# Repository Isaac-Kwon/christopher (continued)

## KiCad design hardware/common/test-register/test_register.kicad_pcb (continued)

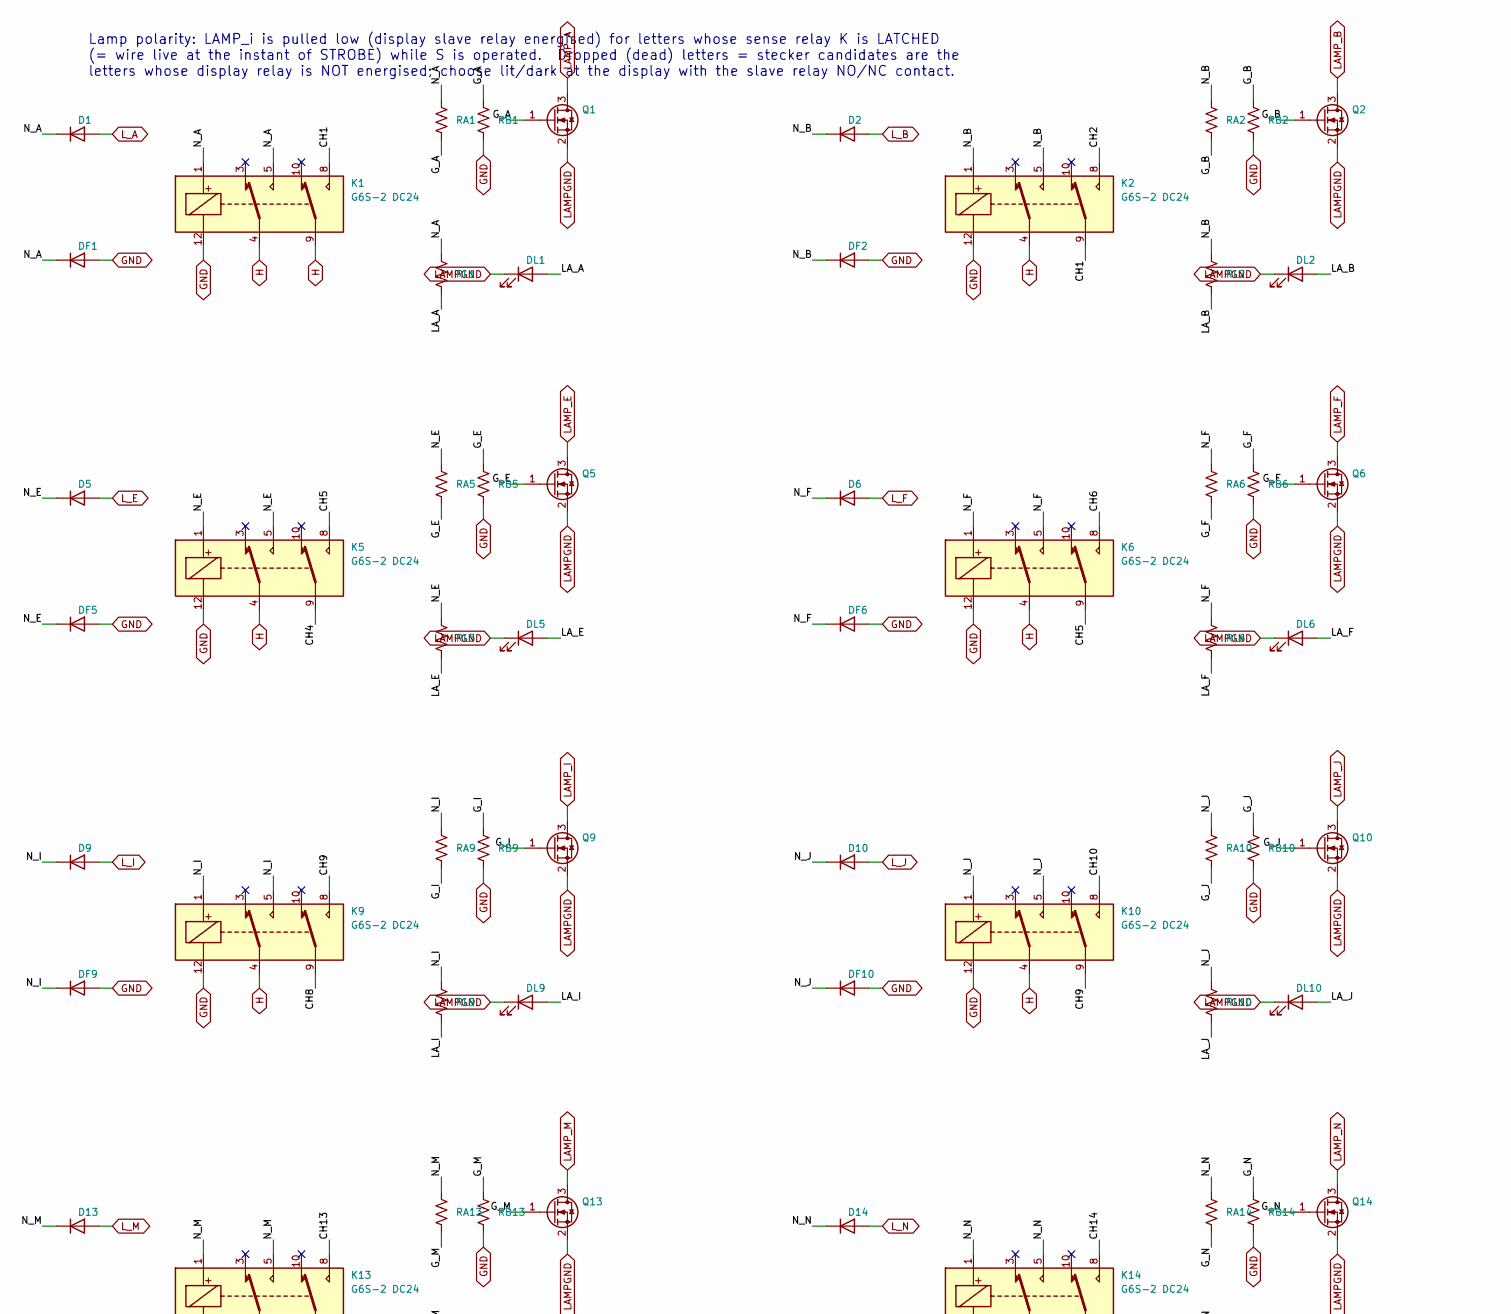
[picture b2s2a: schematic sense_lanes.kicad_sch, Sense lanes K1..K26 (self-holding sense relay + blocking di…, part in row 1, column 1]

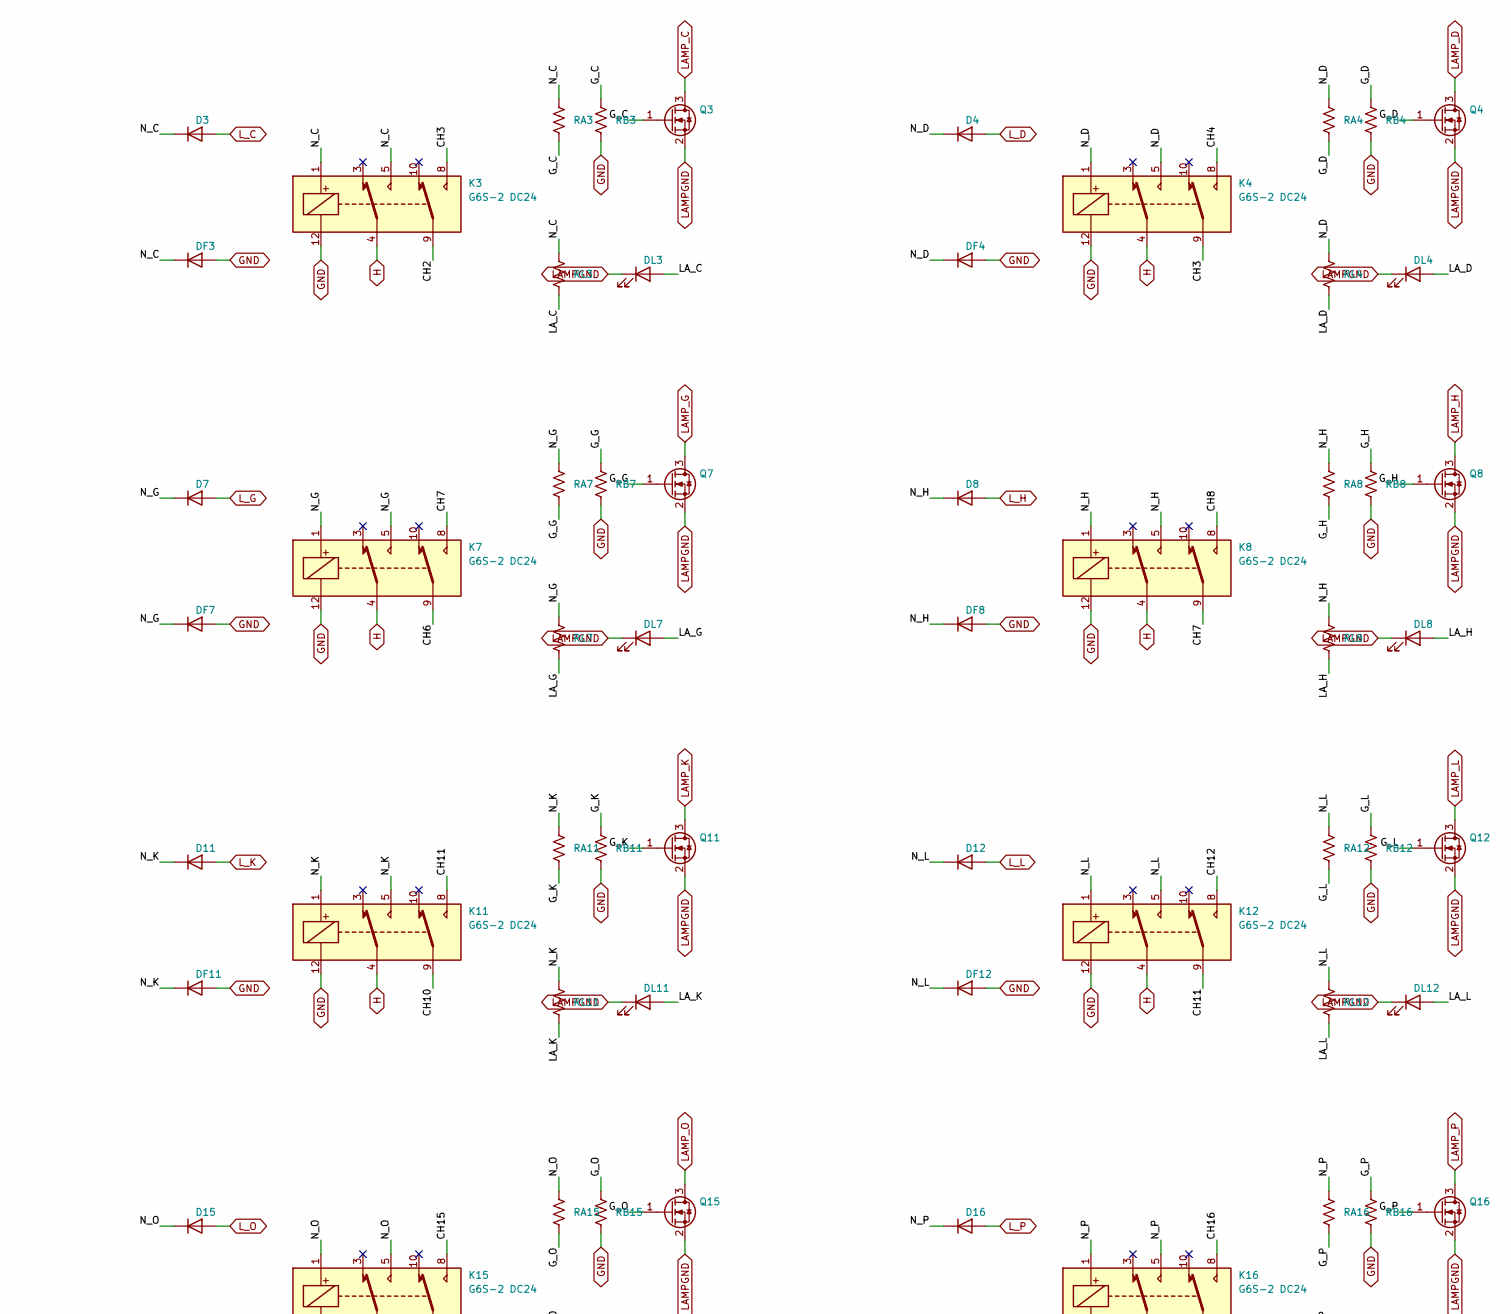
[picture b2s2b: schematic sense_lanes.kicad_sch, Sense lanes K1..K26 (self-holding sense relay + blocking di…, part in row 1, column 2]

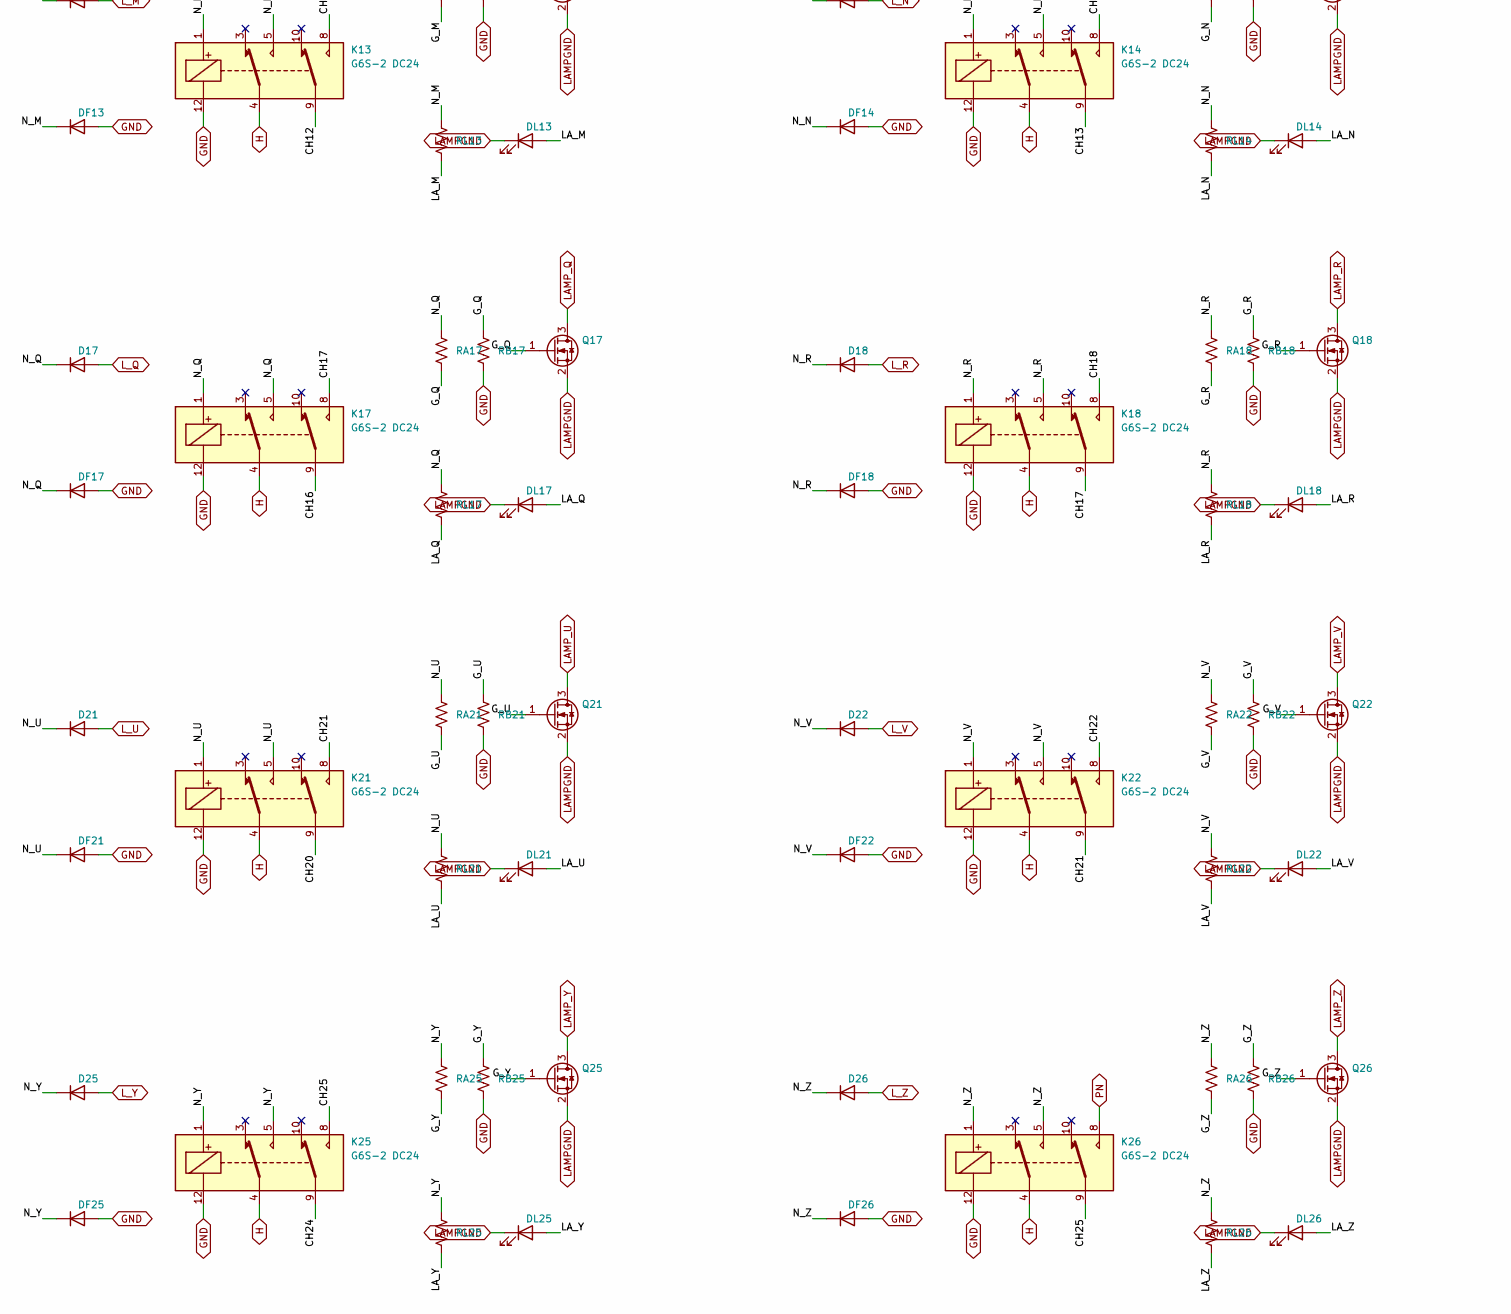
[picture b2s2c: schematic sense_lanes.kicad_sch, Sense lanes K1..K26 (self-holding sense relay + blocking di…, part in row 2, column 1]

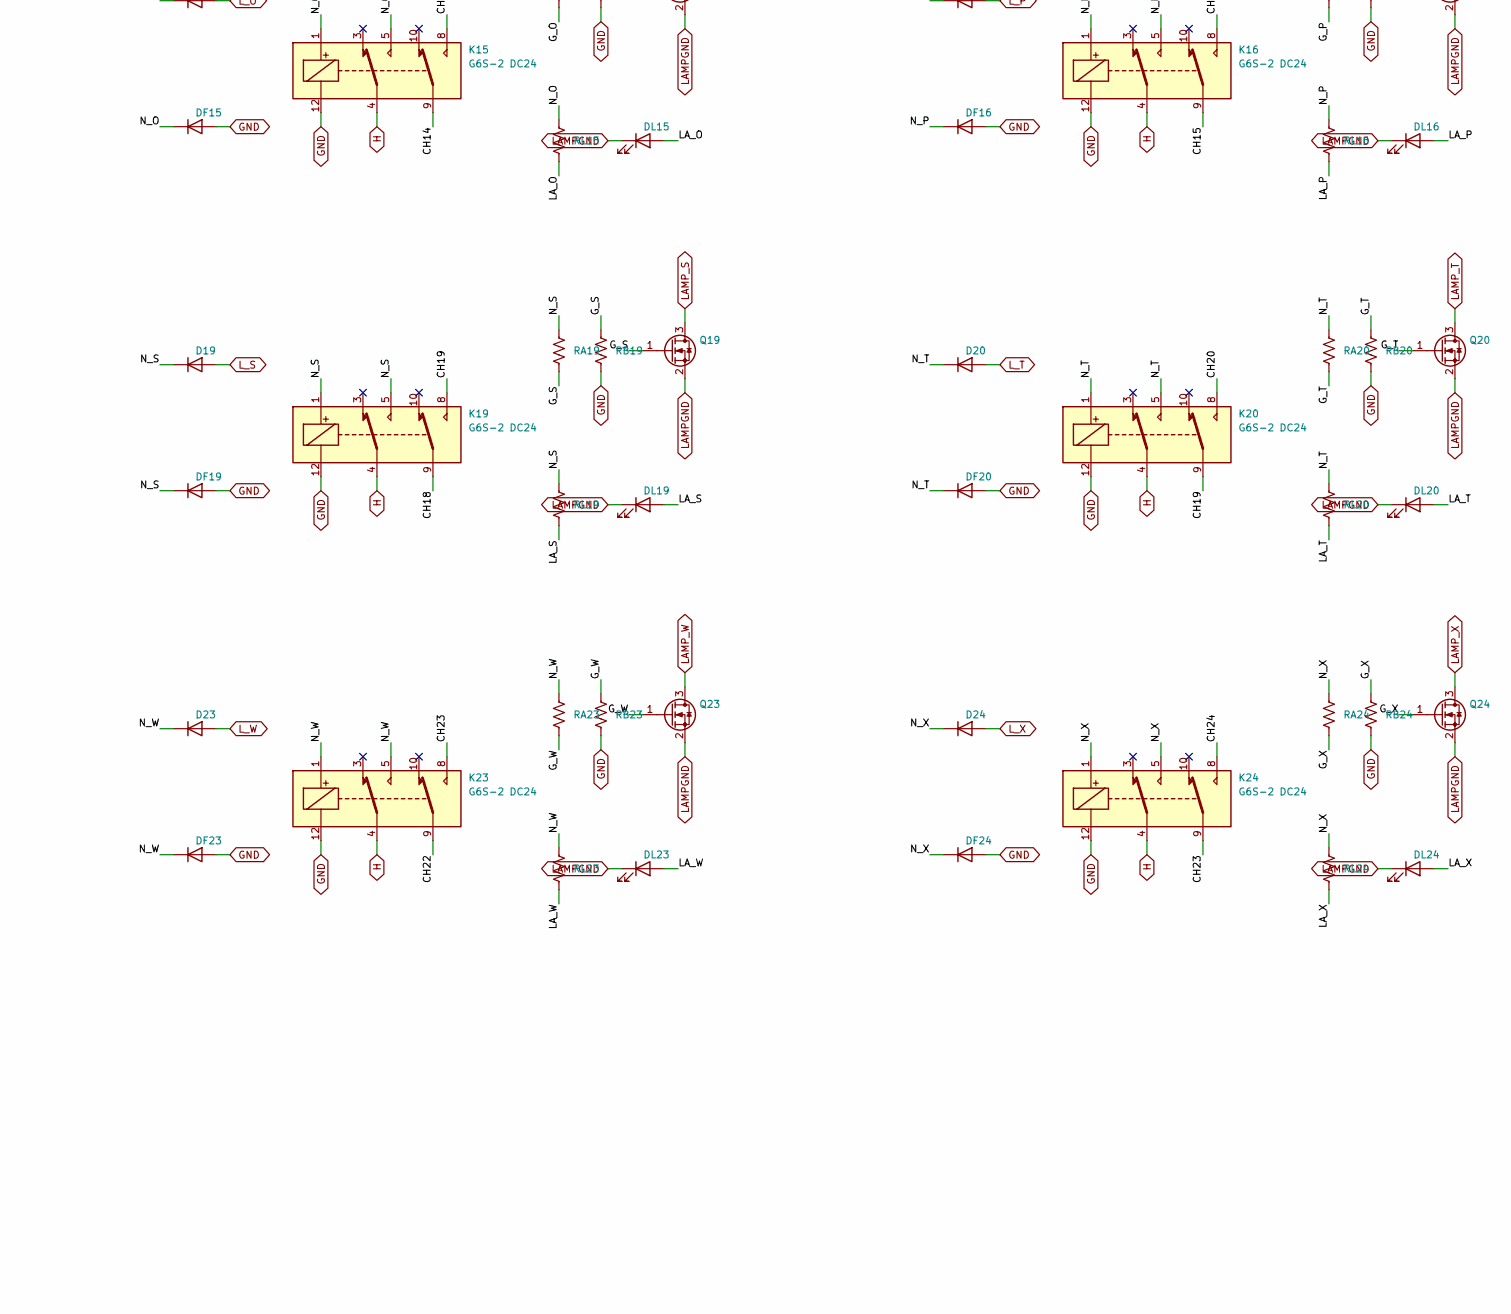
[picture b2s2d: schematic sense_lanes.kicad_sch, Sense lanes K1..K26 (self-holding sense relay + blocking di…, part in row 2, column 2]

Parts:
D1, D2, D3, D4, D5, D6, D7, D8, D9, D10, D11, D12, D13, D14, D15, D16, D17, D18, D19, D20, D21, D22, D23, D24, D25, D26: 1N4148W; D_SOD-123
DF1, DF2, DF3, DF4, DF5, DF6, DF7, DF8, DF9, DF10, DF11, DF12, DF13, DF14, DF15, DF16, DF17, DF18, DF19, DF20, DF21, DF22, DF23, DF24, DF25, DF26: 1N4148W; D_SOD-123
DL1, DL2, DL3, DL4, DL5, DL6, DL7, DL8, DL9, DL10, DL11, DL12, DL13, DL14, DL15, DL16, DL17, DL18, DL19, DL20, DL21, DL22, DL23, DL24, DL25, DL26: LED; LED_0603_1608Metric
K1, K2, K3, K4, K5, K6, K7, K8, K9, K10, K11, K12, K13, K14, K15, K16, K17, K18, K19, K20, K21, K22, K23, K24, K25, K26: G6S-2 DC24; Relay_DPDT_Omron_G6S-2
Q1, Q2, Q3, Q4, Q5, Q6, Q7, Q8, Q9, Q10, Q11, Q12, Q13, Q14, Q15, Q16, Q17, Q18, Q19, Q20, Q21, Q22, Q23, Q24, Q25, Q26: AO3400A; SOT-23
RA1, RA2, RA3, RA4, RA5, RA6, RA7, RA8, RA9, RA10, RA11, RA12, RA13, RA14, RA15, RA16, RA17, RA18, RA19, RA20, RA21, RA22, RA23, RA24, RA25, RA26: 33k; R_0603_1608Metric
RB1, RB2, RB3, RB4, RB5, RB6, RB7, RB8, RB9, RB10, RB11, RB12, RB13, RB14, RB15, RB16, RB17, RB18, RB19, RB20, RB21, RB22, RB23, RB24, RB25, RB26: 22k; R_0603_1608Metric
RL1, RL2, RL3, RL4, RL5, RL6, RL7, RL8, RL9, RL10, RL11, RL12, RL13, RL14, RL15, RL16, RL17, RL18, RL19, RL20, RL21, RL22, RL23, RL24, RL25, RL26: 3.3k; R_0603_1608Metric

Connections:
/SENSE_LANES/CH1: K1.8, K2.9
/SENSE_LANES/CH2: K2.8, K3.9
/SENSE_LANES/CH3: K3.8, K4.9
/SENSE_LANES/CH4: K4.8, K5.9
/SENSE_LANES/CH5: K5.8, K6.9
/SENSE_LANES/CH6: K6.8, K7.9
/SENSE_LANES/CH7: K7.8, K8.9
/SENSE_LANES/CH8: K8.8, K9.9
/SENSE_LANES/CH9: K9.8, K10.9
/SENSE_LANES/CH10: K10.8, K11.9
/SENSE_LANES/CH11: K11.8, K12.9
/SENSE_LANES/CH12: K12.8, K13.9
/SENSE_LANES/CH13: K13.8, K14.9
/SENSE_LANES/CH14: K14.8, K15.9
/SENSE_LANES/CH15: K15.8, K16.9
/SENSE_LANES/CH16: K16.8, K17.9
/SENSE_LANES/CH17: K17.8, K18.9
/SENSE_LANES/CH18: K18.8, K19.9
/SENSE_LANES/CH19: K19.8, K20.9
/SENSE_LANES/CH20: K20.8, K21.9
/SENSE_LANES/CH21: K21.8, K22.9
/SENSE_LANES/CH22: K22.8, K23.9
/SENSE_LANES/CH23: K23.8, K24.9
/SENSE_LANES/CH24: K24.8, K25.9
/SENSE_LANES/CH25: K25.8, K26.9
/SENSE_LANES/G_A: Q1.1 (G), RA1.2, RB1.1
/SENSE_LANES/G_B: Q2.1 (G), RA2.2, RB2.1
/SENSE_LANES/G_C: Q3.1 (G), RA3.2, RB3.1
/SENSE_LANES/G_D: Q4.1 (G), RA4.2, RB4.1
/SENSE_LANES/G_E: Q5.1 (G), RA5.2, RB5.1
/SENSE_LANES/G_F: Q6.1 (G), RA6.2, RB6.1
/SENSE_LANES/G_G: Q7.1 (G), RA7.2, RB7.1
/SENSE_LANES/G_H: Q8.1 (G), RA8.2, RB8.1
/SENSE_LANES/G_I: Q9.1 (G), RA9.2, RB9.1
/SENSE_LANES/G_J: Q10.1 (G), RA10.2, RB10.1
/SENSE_LANES/G_K: Q11.1 (G), RA11.2, RB11.1
/SENSE_LANES/G_L: Q12.1 (G), RA12.2, RB12.1
/SENSE_LANES/G_M: Q13.1 (G), RA13.2, RB13.1
/SENSE_LANES/G_N: Q14.1 (G), RA14.2, RB14.1
/SENSE_LANES/G_O: Q15.1 (G), RA15.2, RB15.1
/SENSE_LANES/G_P: Q16.1 (G), RA16.2, RB16.1
/SENSE_LANES/G_Q: Q17.1 (G), RA17.2, RB17.1
/SENSE_LANES/G_R: Q18.1 (G), RA18.2, RB18.1
/SENSE_LANES/G_S: Q19.1 (G), RA19.2, RB19.1
/SENSE_LANES/G_T: Q20.1 (G), RA20.2, RB20.1
/SENSE_LANES/G_U: Q21.1 (G), RA21.2, RB21.1
/SENSE_LANES/G_V: Q22.1 (G), RA22.2, RB22.1
/SENSE_LANES/G_W: Q23.1 (G), RA23.2, RB23.1
/SENSE_LANES/G_X: Q24.1 (G), RA24.2, RB24.1
/SENSE_LANES/G_Y: Q25.1 (G), RA25.2, RB25.1
/SENSE_LANES/G_Z: Q26.1 (G), RA26.2, RB26.1
/SENSE_LANES/LA_A: DL1.2 (A), RL1.2
/SENSE_LANES/LA_B: DL2.2 (A), RL2.2
/SENSE_LANES/LA_C: DL3.2 (A), RL3.2
/SENSE_LANES/LA_D: DL4.2 (A), RL4.2
/SENSE_LANES/LA_E: DL5.2 (A), RL5.2
/SENSE_LANES/LA_F: DL6.2 (A), RL6.2
/SENSE_LANES/LA_G: DL7.2 (A), RL7.2
/SENSE_LANES/LA_H: DL8.2 (A), RL8.2
/SENSE_LANES/LA_I: DL9.2 (A), RL9.2
/SENSE_LANES/LA_J: DL10.2 (A), RL10.2
/SENSE_LANES/LA_K: DL11.2 (A), RL11.2
/SENSE_LANES/LA_L: DL12.2 (A), RL12.2
/SENSE_LANES/LA_M: DL13.2 (A), RL13.2
/SENSE_LANES/LA_N: DL14.2 (A), RL14.2
/SENSE_LANES/LA_O: DL15.2 (A), RL15.2
/SENSE_LANES/LA_P: DL16.2 (A), RL16.2
/SENSE_LANES/LA_Q: DL17.2 (A), RL17.2
/SENSE_LANES/LA_R: DL18.2 (A), RL18.2
/SENSE_LANES/LA_S: DL19.2 (A), RL19.2
/SENSE_LANES/LA_T: DL20.2 (A), RL20.2
/SENSE_LANES/LA_U: DL21.2 (A), RL21.2
/SENSE_LANES/LA_V: DL22.2 (A), RL22.2
/SENSE_LANES/LA_W: DL23.2 (A), RL23.2
/SENSE_LANES/LA_X: DL24.2 (A), RL24.2
/SENSE_LANES/LA_Y: DL25.2 (A), RL25.2
/SENSE_LANES/LA_Z: DL26.2 (A), RL26.2
/SENSE_LANES/N_A: D1.1 (K), DF1.1 (K), K1.1, K1.5, RA1.1, RL1.1
/SENSE_LANES/N_B: D2.1 (K), DF2.1 (K), K2.1, K2.5, RA2.1, RL2.1
/SENSE_LANES/N_C: D3.1 (K), DF3.1 (K), K3.1, K3.5, RA3.1, RL3.1
/SENSE_LANES/N_D: D4.1 (K), DF4.1 (K), K4.1, K4.5, RA4.1, RL4.1
/SENSE_LANES/N_E: D5.1 (K), DF5.1 (K), K5.1, K5.5, RA5.1, RL5.1
/SENSE_LANES/N_F: D6.1 (K), DF6.1 (K), K6.1, K6.5, RA6.1, RL6.1
/SENSE_LANES/N_G: D7.1 (K), DF7.1 (K), K7.1, K7.5, RA7.1, RL7.1
/SENSE_LANES/N_H: D8.1 (K), DF8.1 (K), K8.1, K8.5, RA8.1, RL8.1
/SENSE_LANES/N_I: D9.1 (K), DF9.1 (K), K9.1, K9.5, RA9.1, RL9.1
/SENSE_LANES/N_J: D10.1 (K), DF10.1 (K), K10.1, K10.5, RA10.1, RL10.1
/SENSE_LANES/N_K: D11.1 (K), DF11.1 (K), K11.1, K11.5, RA11.1, RL11.1
/SENSE_LANES/N_L: D12.1 (K), DF12.1 (K), K12.1, K12.5, RA12.1, RL12.1
/SENSE_LANES/N_M: D13.1 (K), DF13.1 (K), K13.1, K13.5, RA13.1, RL13.1
/SENSE_LANES/N_N: D14.1 (K), DF14.1 (K), K14.1, K14.5, RA14.1, RL14.1
/SENSE_LANES/N_O: D15.1 (K), DF15.1 (K), K15.1, K15.5, RA15.1, RL15.1
/SENSE_LANES/N_P: D16.1 (K), DF16.1 (K), K16.1, K16.5, RA16.1, RL16.1
/SENSE_LANES/N_Q: D17.1 (K), DF17.1 (K), K17.1, K17.5, RA17.1, RL17.1
/SENSE_LANES/N_R: D18.1 (K), DF18.1 (K), K18.1, K18.5, RA18.1, RL18.1
/SENSE_LANES/N_S: D19.1 (K), DF19.1 (K), K19.1, K19.5, RA19.1, RL19.1
/SENSE_LANES/N_T: D20.1 (K), DF20.1 (K), K20.1, K20.5, RA20.1, RL20.1
/SENSE_LANES/N_U: D21.1 (K), DF21.1 (K), K21.1, K21.5, RA21.1, RL21.1
/SENSE_LANES/N_V: D22.1 (K), DF22.1 (K), K22.1, K22.5, RA22.1, RL22.1
/SENSE_LANES/N_W: D23.1 (K), DF23.1 (K), K23.1, K23.5, RA23.1, RL23.1
/SENSE_LANES/N_X: D24.1 (K), DF24.1 (K), K24.1, K24.5, RA24.1, RL24.1
/SENSE_LANES/N_Y: D25.1 (K), DF25.1 (K), K25.1, K25.5, RA25.1, RL25.1
/SENSE_LANES/N_Z: D26.1 (K), DF26.1 (K), K26.1, K26.5, RA26.1, RL26.1
GND: DF1.2 (A), DF2.2 (A), DF3.2 (A), DF4.2 (A), DF5.2 (A), DF6.2 (A), DF7.2 (A), DF8.2 (A), DF9.2 (A), DF10.2 (A), DF11.2 (A), DF12.2 (A), DF13.2 (A), DF14.2 (A), DF15.2 (A), DF16.2 (A), DF17.2 (A), DF18.2 (A), DF19.2 (A), DF20.2 (A), DF21.2 (A), DF22.2 (A), DF23.2 (A), DF24.2 (A), DF25.2 (A), DF26.2 (A), K1.12, K2.12, K3.12, K4.12, K5.12, K6.12, K7.12, K8.12, K9.12, K10.12, K11.12, K12.12, K13.12, K14.12, K15.12, K16.12, K17.12, K18.12, K19.12, K20.12, K21.12, K22.12, K23.12, K24.12, K25.12, K26.12, RB1.2, RB2.2, RB3.2, RB4.2, RB5.2, RB6.2, RB7.2, RB8.2, RB9.2, RB10.2, RB11.2, RB12.2, RB13.2, RB14.2, RB15.2, RB16.2, RB17.2, RB18.2, RB19.2, RB20.2, RB21.2, RB22.2, RB23.2, RB24.2, RB25.2, RB26.2; also elsewhere on the board
H: K1.4, K1.9, K2.4, K3.4, K4.4, K5.4, K6.4, K7.4, K8.4, K9.4, K10.4, K11.4, K12.4, K13.4, K14.4, K15.4, K16.4, K17.4, K18.4, K19.4, K20.4, K21.4, K22.4, K23.4, K24.4, K25.4, K26.4; also elsewhere on the board
LAMPGND: DL1.1 (K), DL2.1 (K), DL3.1 (K), DL4.1 (K), DL5.1 (K), DL6.1 (K), DL7.1 (K), DL8.1 (K), DL9.1 (K), DL10.1 (K), DL11.1 (K), DL12.1 (K), DL13.1 (K), DL14.1 (K), DL15.1 (K), DL16.1 (K), DL17.1 (K), DL18.1 (K), DL19.1 (K), DL20.1 (K), DL21.1 (K), DL22.1 (K), DL23.1 (K), DL24.1 (K), DL25.1 (K), DL26.1 (K), Q1.2 (S), Q2.2 (S), Q3.2 (S), Q4.2 (S), Q5.2 (S), Q6.2 (S), Q7.2 (S), Q8.2 (S), Q9.2 (S), Q10.2 (S), Q11.2 (S), Q12.2 (S), Q13.2 (S), Q14.2 (S), Q15.2 (S), Q16.2 (S), Q17.2 (S), Q18.2 (S), Q19.2 (S), Q20.2 (S), Q21.2 (S), Q22.2 (S), Q23.2 (S), Q24.2 (S), Q25.2 (S), Q26.2 (S); also elsewhere on the board
LAMP_A: Q1.3 (D); also elsewhere on the board
LAMP_B: Q2.3 (D); also elsewhere on the board
LAMP_C: Q3.3 (D); also elsewhere on the board
LAMP_D: Q4.3 (D); also elsewhere on the board
LAMP_E: Q5.3 (D); also elsewhere on the board
LAMP_F: Q6.3 (D); also elsewhere on the board
LAMP_G: Q7.3 (D); also elsewhere on the board
LAMP_H: Q8.3 (D); also elsewhere on the board
LAMP_I: Q9.3 (D); also elsewhere on the board
LAMP_J: Q10.3 (D); also elsewhere on the board
LAMP_K: Q11.3 (D); also elsewhere on the board
LAMP_L: Q12.3 (D); also elsewhere on the board
LAMP_M: Q13.3 (D); also elsewhere on the board
LAMP_N: Q14.3 (D); also elsewhere on the board
LAMP_O: Q15.3 (D); also elsewhere on the board
LAMP_P: Q16.3 (D); also elsewhere on the board
LAMP_Q: Q17.3 (D); also elsewhere on the board
LAMP_R: Q18.3 (D); also elsewhere on the board
LAMP_S: Q19.3 (D); also elsewhere on the board
LAMP_T: Q20.3 (D); also elsewhere on the board
LAMP_U: Q21.3 (D); also elsewhere on the board
LAMP_V: Q22.3 (D); also elsewhere on the board
LAMP_W: Q23.3 (D); also elsewhere on the board
LAMP_X: Q24.3 (D); also elsewhere on the board
LAMP_Y: Q25.3 (D); also elsewhere on the board
LAMP_Z: Q26.3 (D); also elsewhere on the board
L_A: D1.2 (A); also elsewhere on the board
L_B: D2.2 (A); also elsewhere on the board
L_C: D3.2 (A); also elsewhere on the board
L_D: D4.2 (A); also elsewhere on the board
L_E: D5.2 (A); also elsewhere on the board
L_F: D6.2 (A); also elsewhere on the board
L_G: D7.2 (A); also elsewhere on the board
L_H: D8.2 (A); also elsewhere on the board
L_I: D9.2 (A); also elsewhere on the board
L_J: D10.2 (A); also elsewhere on the board
L_K: D11.2 (A); also elsewhere on the board
L_L: D12.2 (A); also elsewhere on the board
L_M: D13.2 (A); also elsewhere on the board
L_N: D14.2 (A); also elsewhere on the board
L_O: D15.2 (A); also elsewhere on the board
L_P: D16.2 (A); also elsewhere on the board
L_Q: D17.2 (A); also elsewhere on the board
L_R: D18.2 (A); also elsewhere on the board
L_S: D19.2 (A); also elsewhere on the board
L_T: D20.2 (A); also elsewhere on the board
L_U: D21.2 (A); also elsewhere on the board
L_V: D22.2 (A); also elsewhere on the board
L_W: D23.2 (A); also elsewhere on the board
L_X: D24.2 (A); also elsewhere on the board
L_Y: D25.2 (A); also elsewhere on the board
L_Z: D26.2 (A); also elsewhere on the board
PN: K26.8; also elsewhere on the board

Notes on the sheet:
Lamp polarity: LAMP_i is pulled low (display slave relay energised) for letters whose sense relay K is LATCHED (= wire live at the instant of STROBE) while S is operated. Dropped (dead) letters = stecker candidates are the letters whose display relay is NOT energised; choose lit/dark at the display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

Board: 2 copper layers, 269 parts (0 on the bottom side), 198 nets, no tracks yet.

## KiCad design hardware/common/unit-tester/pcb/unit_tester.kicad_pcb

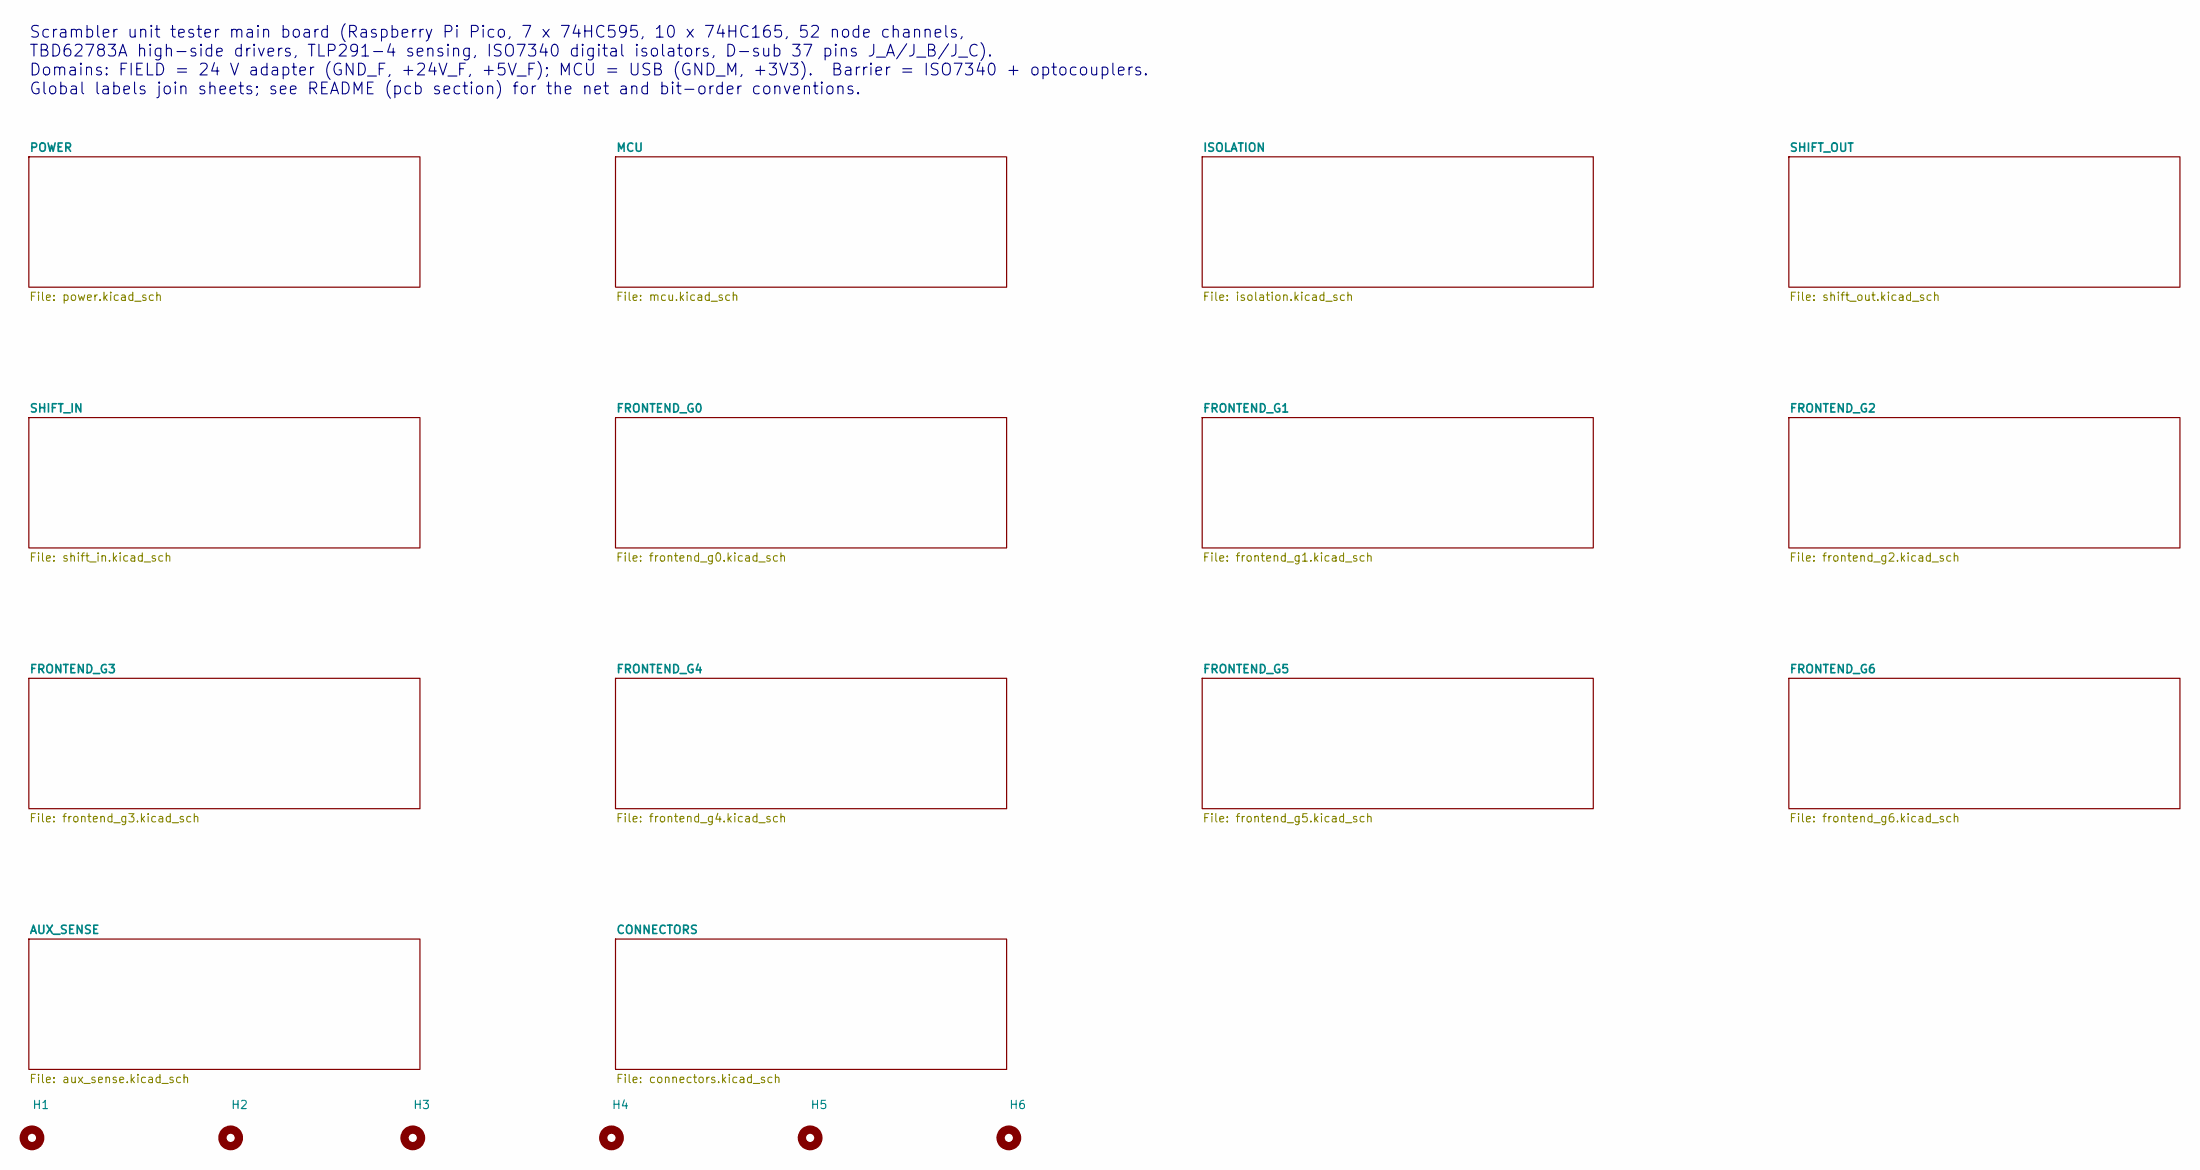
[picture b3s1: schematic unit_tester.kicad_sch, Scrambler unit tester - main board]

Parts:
H1, H2, H3, H4, H5, H6: M3; MountingHole_3.2mm_M3

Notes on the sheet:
Scrambler unit tester main board (Raspberry Pi Pico, 7 x 74HC595, 10 x 74HC165, 52 node channels, TBD62783A high-side drivers, TLP291-4 sensing, ISO7340 digital isolators, D-sub 37 pins J_A/J_B/J_C). Domains: FIELD = 24 V adapter (GND_F, +24V_F, +5V_F); MCU = USB (GND_M, +3V3). Barrier = ISO7340 + 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

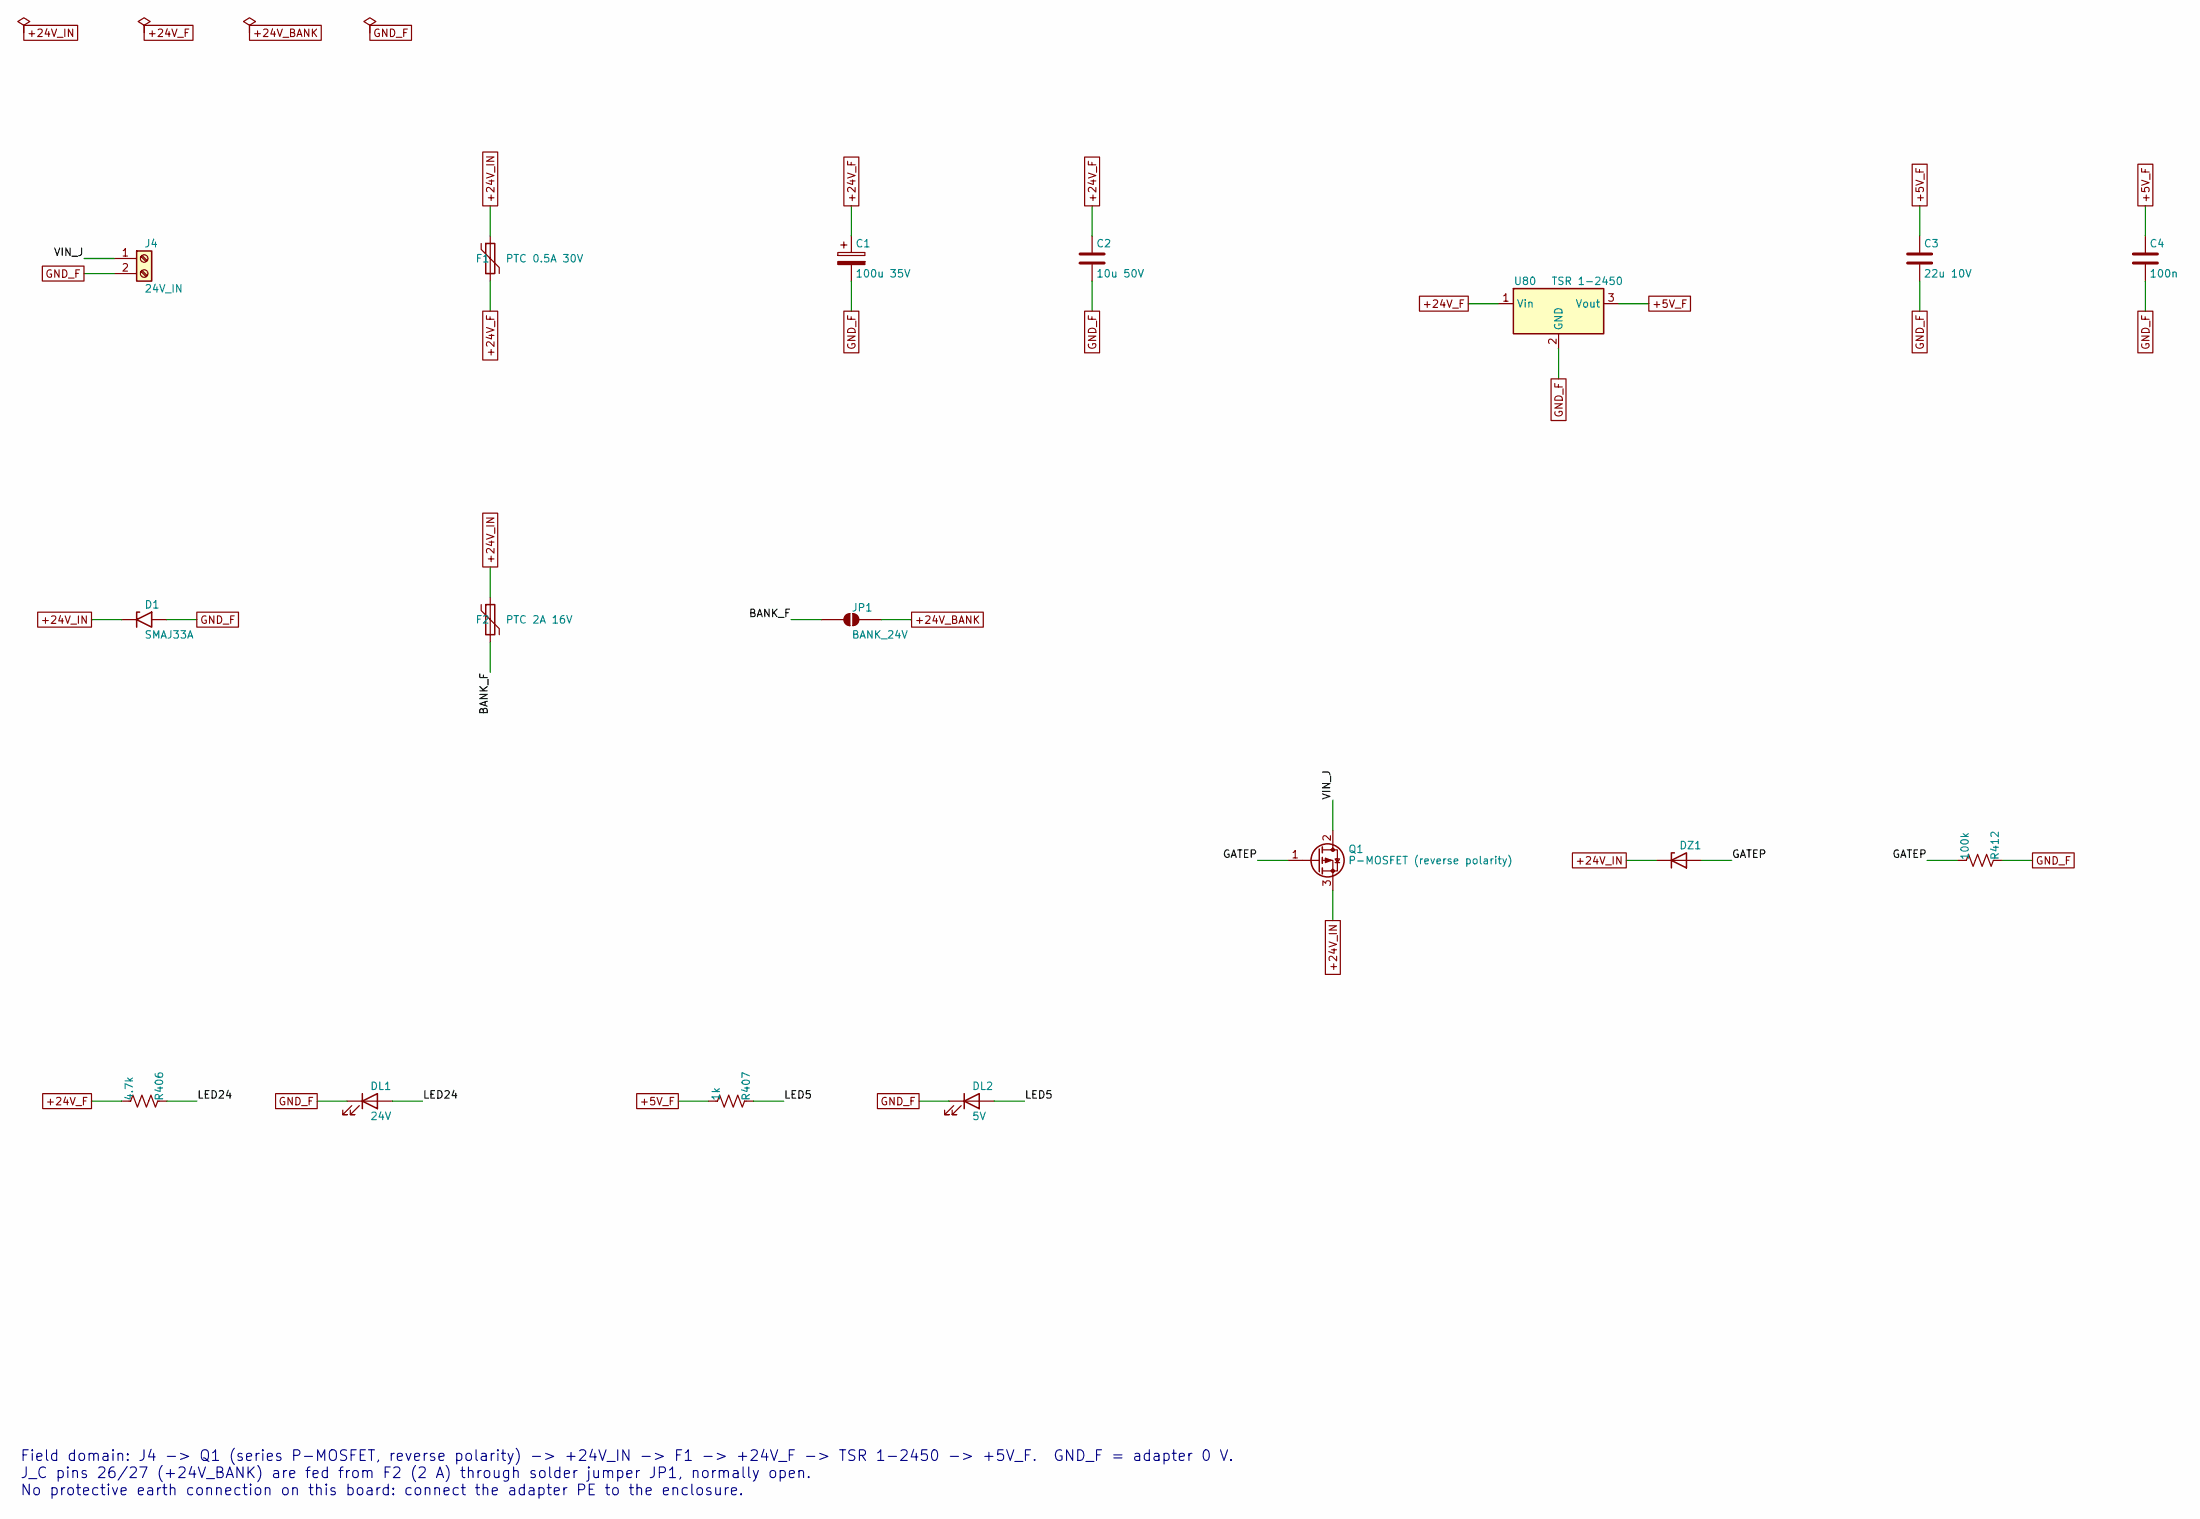
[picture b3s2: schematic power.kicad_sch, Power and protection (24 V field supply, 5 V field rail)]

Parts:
C1: 100u 35V; CP_Elec_8x10
C2: 10u 50V; C_1206_3216Metric
C3: 22u 10V; C_1206_3216Metric
C4: 100n; C_0603_1608Metric
D1: SMAJ33A; D_SMA
DL1: 24V; LED_0603_1608Metric
DL2: 5V; LED_0603_1608Metric
DZ1: 12V; D_SOD-123
F1: PTC 0.5A 30V; Fuse_1812_4532Metric
F2: PTC 2A 16V; Fuse_2920_7451Metric
J4: 24V_IN; TerminalBlock_Phoenix_MKDS-1,5-2-5.08_1x02_P5.08mm_Horizont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
JP1: BANK_24V; SolderJumper-2_P1.3mm_Open_RoundedPad1.0x1.5mm
Q1: P-MOSFET (reverse polarity); SOT-223-3_TabPin2
R406: 4.7k; R_0603_1608Metric
R407: 1k; R_0603_1608Metric
R412: 100k; R_0603_1608Metric
U80: TSR 1-2450; Converter_DCDC_TRACO_TSR-1_THT

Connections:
+5V_F: C3.1, C4.1, R407.1, U80.3 (Vout); also elsewhere on the board
+24V_BANK: JP1.2 (B); also elsewhere on the board
+24V_F: C1.1, C2.1, F1.2, R406.1, U80.1 (Vin); also elsewhere on the board
+24V_IN: D1.1 (A1), DZ1.1 (K), F1.1, F2.1, Q1.3 (S)
/POWER/BANK_F: F2.2, JP1.1 (A)
/POWER/GATEP: DZ1.2 (A), Q1.1 (G), R412.1
/POWER/LED5: DL2.2 (A), R407.2
/POWER/LED24: DL1.2 (A), R406.2
/POWER/VIN_J: J4.1, Q1.2 (D)
GND_F: C1.2, C2.2, C3.2, C4.2, D1.2 (A2), DL1.1 (K), DL2.1 (K), J4.2, R412.2, U80.2 (GND); also elsewhere on the board

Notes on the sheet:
Field domain: J4 -> Q1 (series P-MOSFET, reverse polarity) -> +24V_IN -> F1 -> +24V_F -> TSR 1-2450 -> +5V_F. GND_F = adapter 0 V. J_C pins 26/27 (+24V_BANK) are fed from F2 (2 A) through solder jumper JP1, normally open. No protective earth connection on this board: connect the adapter PE to the e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
